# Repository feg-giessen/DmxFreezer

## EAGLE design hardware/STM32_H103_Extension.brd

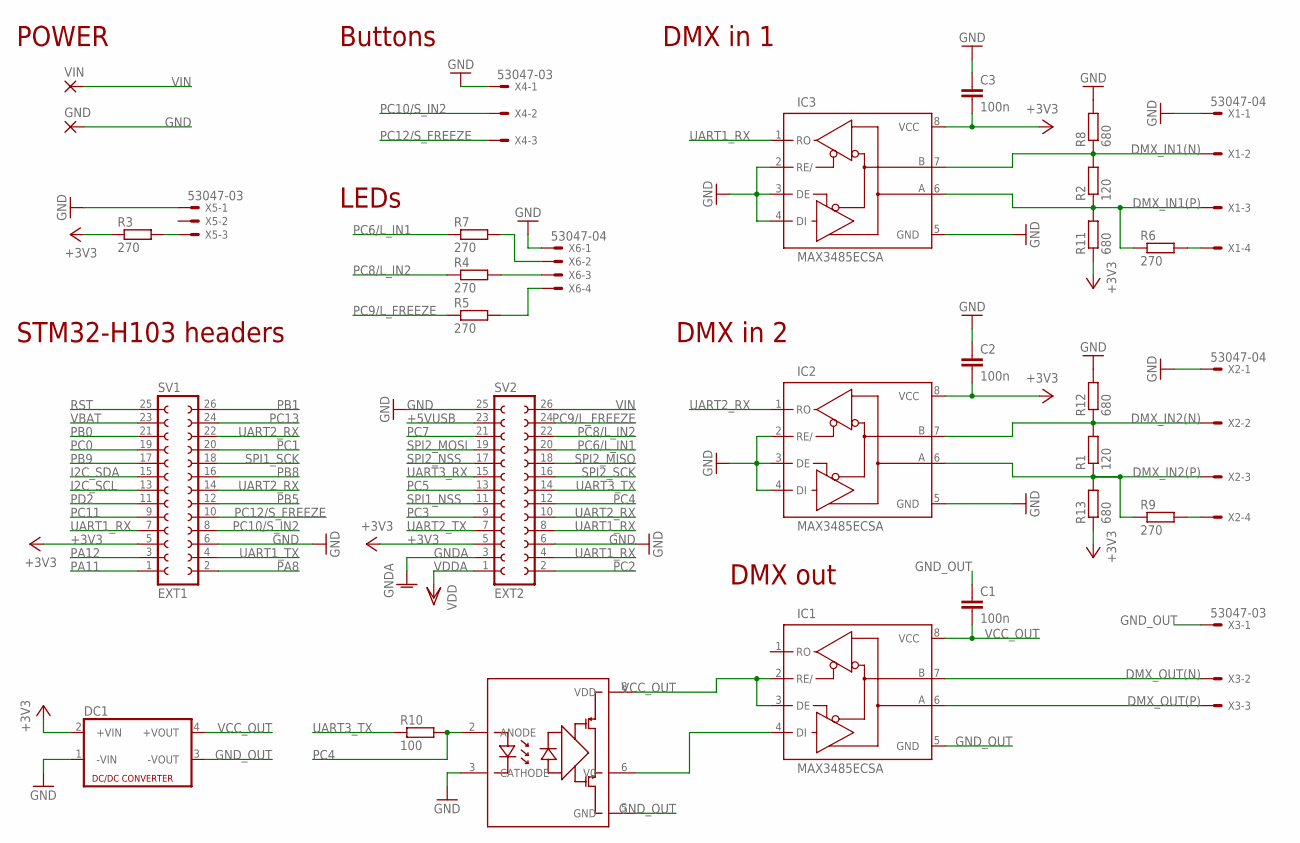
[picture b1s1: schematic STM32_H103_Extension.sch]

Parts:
C1, C2, C3: 100n; C0603
DC1: NME
GND: 2,15/1,0
IC1, IC2, IC3: MAX3485ECSA; SO08
R1, R2: 120; R0603
R3, R4, R5, R6, R7, R9: 270; R0603
R8, R11, R12, R13: 680; R0603
R10: 100; R0603
SV1: EXT1; FE13-2
SV2: EXT2; FE13-2
U1: ACPL-071L; SOIC-8
VIN: 2,15/1,0
X1, X2, X6: 53047-04
X3, X4, X5: 53047-03

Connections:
+3V3: C2.2, C3.2, DC1.2 (+VIN), IC2.8 (VCC), IC3.8 (VCC), R3.1, R11.1, R13.1, SV1.5, SV2.5
+5VUSB: SV2.23
DMX_IN1(N): IC3.7 (B), R2.2, R8.1, X1.2
DMX_IN1(P): IC3.6 (A), R2.1, R6.1, R11.2, X1.3
DMX_IN2(N): IC2.7 (B), R1.2, R12.1, X2.2
DMX_IN2(P): IC2.6 (A), R1.1, R9.1, R13.2, X2.3
DMX_OUT(N): IC1.7 (B), X3.2
DMX_OUT(P): IC1.6 (A), X3.3
GND: C2.1, C3.1, DC1.1 (-VIN), GND.1, IC2.2 (RE/), IC2.3 (DE), IC2.4 (DI), IC2.5 (GND), IC3.2 (RE/), IC3.3 (DE), IC3.4 (DI), IC3.5 (GND), R8.2, R12.2, SV1.6, SV2.6, SV2.25, U1.3 (CATHODE), X1.1, X2.1, X4.1, X5.1, X6.1
GNDA: SV2.3
GND_OUT: C1.1, DC1.3 (-VOUT), IC1.5 (GND), U1.5 (GND), X3.1
I2C_SCL: SV1.13
I2C_SDA: SV1.15
unnamed: R3.2, X5.3
unnamed: R4.2, X6.3
unnamed: R5.2, X6.4
unnamed: R7.2, X6.2
unnamed: IC1.4 (DI), U1.6 (V0)
unnamed: R6.2, X1.4
unnamed: R9.2, X2.4
PA8: SV1.2
PA11: SV1.1
PA12: SV1.3
PB0: SV1.21
PB1: SV1.26
PB5: SV1.12
PB8: SV1.16
PB9: SV1.17
PC0: SV1.19
PC1: SV1.20
PC2: SV2.2
PC3: SV2.9
PC4: R10.2, SV2.12, U1.2 (ANODE)
PC5: SV2.13
PC6/L_IN1: R7.1, SV2.20
PC7: SV2.21
PC8/L_IN2: R4.1, SV2.22
PC9/L_FREEZE: R5.1, SV2.24
PC10/S_IN2: SV1.8, X4.2
PC11: SV1.9
PC12/S_FREEZE: SV1.10, X4.3
PC13: SV1.24
PD2: SV1.11
RST: SV1.25
SPI1_NSS: SV2.11
SPI1_SCK: SV1.18
SPI2_MISO: SV2.18
SPI2_MOSI: SV2.19
SPI2_NSS: SV2.17
SPI2_SCK: SV2.16
UART1_RX: IC3.1 (RO), SV1.7, SV2.4, SV2.8
UART1_TX: SV1.4
UART2_RX: IC2.1 (RO), SV1.14, SV1.22, SV2.10
UART2_TX: SV2.7
UART3_RX: SV2.15
UART3_TX: R10.1, SV2.14
VBAT: SV1.23
VCC_OUT: C1.2, DC1.4 (+VOUT), IC1.2 (RE/), IC1.3 (DE), IC1.8 (VCC), U1.8 (VDD)
VDDA: SV2.1
VIN: SV2.26, VIN.1

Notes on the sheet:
POWER
Buttons
DMX in 1
DMX in 2
DMX out
STM32-H103 headers
LEDs

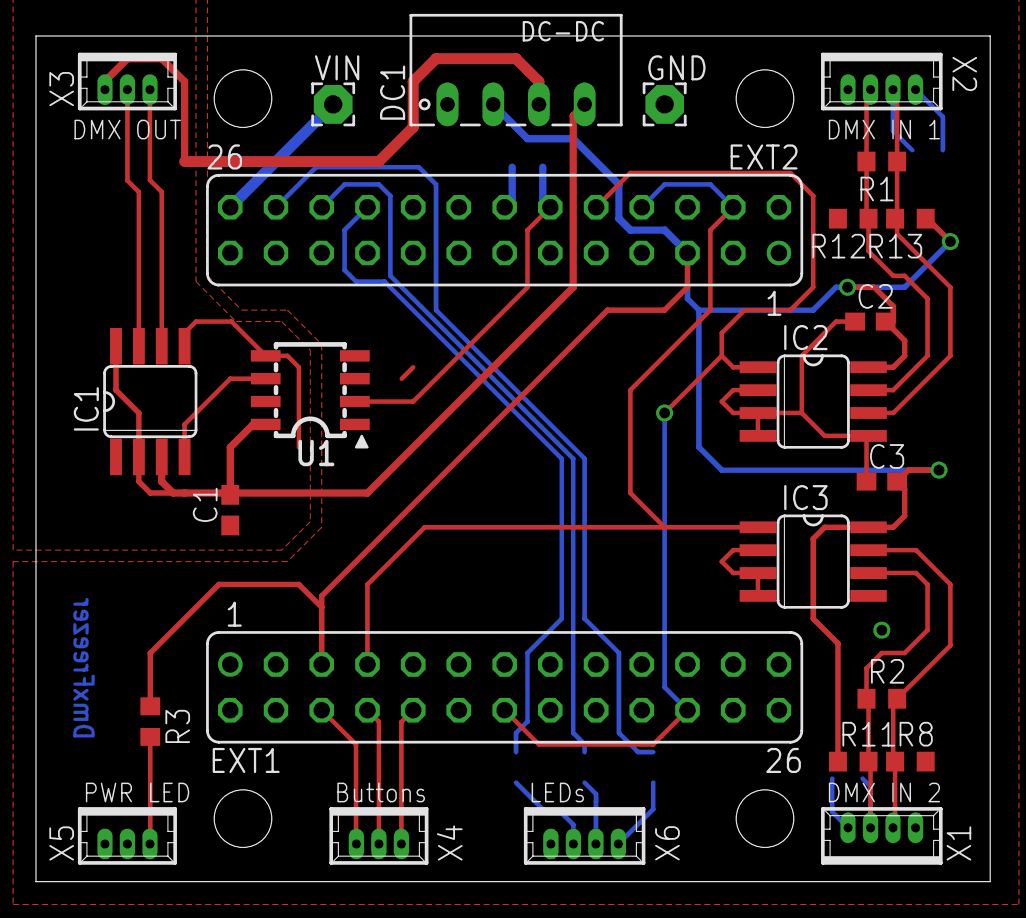
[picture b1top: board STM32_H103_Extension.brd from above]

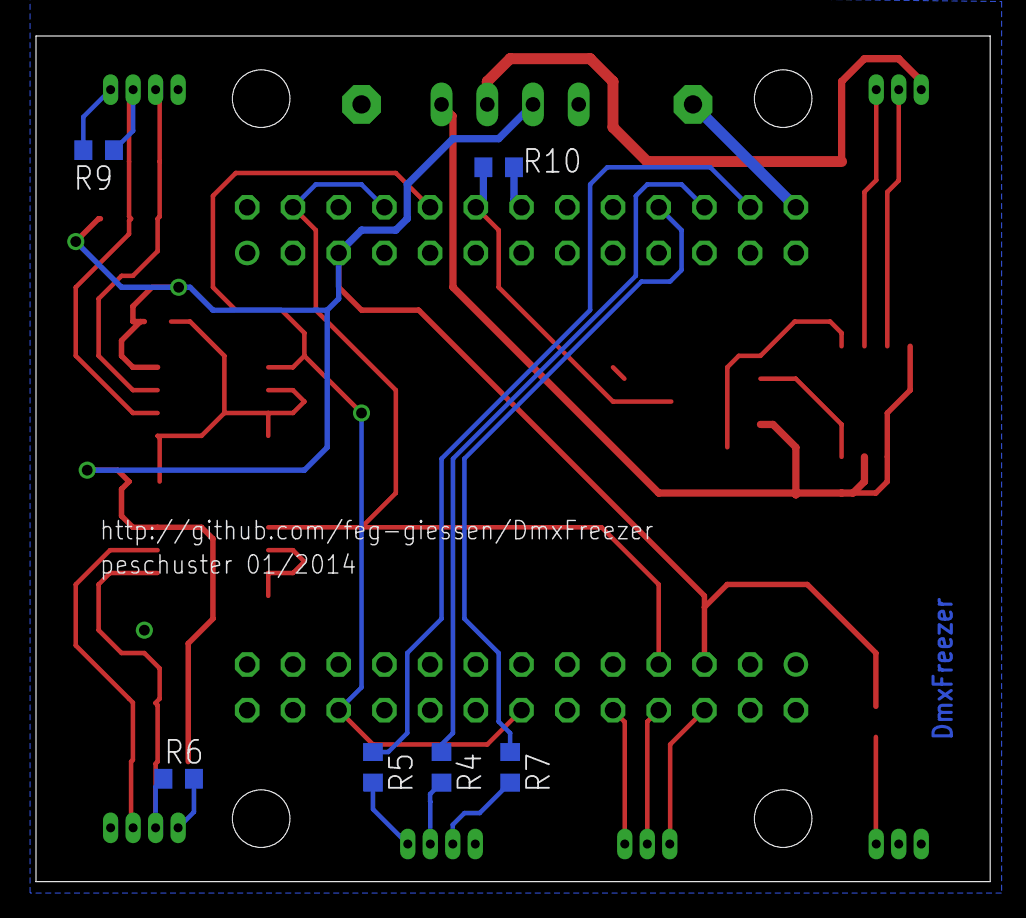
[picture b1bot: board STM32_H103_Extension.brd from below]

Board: 2 copper layers, 53.0 x 47.0 mm, 31 parts (6 on the bottom side), 27 nets.

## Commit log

2014-01-12 STM32F103RB docs
2014-01-12 Initial code commit (blink demo)
2014-01-13 More documentation pdfs.
2014-01-13 First board layout draft.
2014-01-13 Enclosure draft.
2014-01-13 exclude temp egale files.
2014-01-15 OS config tests.
2014-01-15 Moved firmware for os and standalone tests.
